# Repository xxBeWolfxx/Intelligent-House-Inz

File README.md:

# Projekt, praca dyplomowa pod tytułem "Układ sterowania inteligentnego budynku mieszkalnego "
Projekt został zrealizowany w ramach pracy dyplomowej na uczelni wyższej, Politechniki Poznańskiej. Miała ona na celu opracowania systemu do zarządzania domostwem.

## Założenia aplikacji: 
### Funkcje aplikacji:
   - Opracowanie układu kontroli i sterowania budynkiem mieszkalnym
   - Opracowanie mobilnego interfejsu uzytkownika
   - Opracowanie układu komunikacji głosowej

Aplikacja składa się z 4 elementów: Komputera (asystent Google'a, serwer, baza danych), Aplikacja (interfejs użytkownika), ESP Sensors (pobieranie danych z czujników), ESP Outputs (zarządzanie załączaniem urządzeń).
## Komputer.

Jako komputer został zaimplementowany komputer Raspberry Pi 4B, który posiada w sobie instancje:
#### Serwer.
Został zrealizowany za pomocą frameworku Django oraz Django REST framework. Została stworzona strona administracyjna do szybkiego modelowania informacji w bazie.
Link: https://github.com/xxBeWolfxx/Django-server

### Baza danych.
Ze względu na wykorzystanie systemu operacyjnego Debian została zaimplementowana baza SQL w dystrybucji MariaDB. Baza posiada tablice: Użytkownik, ESP Sensor, ESP Output. Tablice ESP Sensor oraz ESP Output są w relacji Many-to-Many z tablicą Użytkownik.

#### Asystent.
Asystent został zaimplementowany jako gotowe rozwiązanie GassistPI[www] https://gassistpi-documentation.readthedocs.io. Wymieniony SDK korzysta z rozwiązań Asystenta Google'a. Zostały również dodane skrypty do sterowania płytką ESP Outputs. 

### Płytki PCB.
Zaprojektowano dwa typy płytek w programie Eagle, które są uniwersalne i mają możliwość podłączenia różnych urządzeń. Napięcie zasilające może osiągać wartość od 10 do 20 Voltów DC. 
#### ESP Sensors
Zawiera:
- 4 porty ADC (2x port z 5V, 2x port 3V3),
- 5 portów kontaktronów, badanie statusu pinów czy zostały zwarte czy rozwarte.
- 4 porty magistrali I2C (2x port z 5V, 2x port 3V3).

#### ESP Outputs
- 5 portów przekaźnikowych zasilonych napięciem zasilania. 
- 2 porty do sterowania silnikiem DC.

### Aplikacja
Składa się ona z dwóch aktywności: uwierzytelnienie użytkownika oraz zarządzanie urządzeniami i sensorami w sieci. Zaimplementowano wykresy wartości czujników. Aplikacja współpracuje ściśle z serwerem i komunikuje się z nim po protokole HTTP REST Api.

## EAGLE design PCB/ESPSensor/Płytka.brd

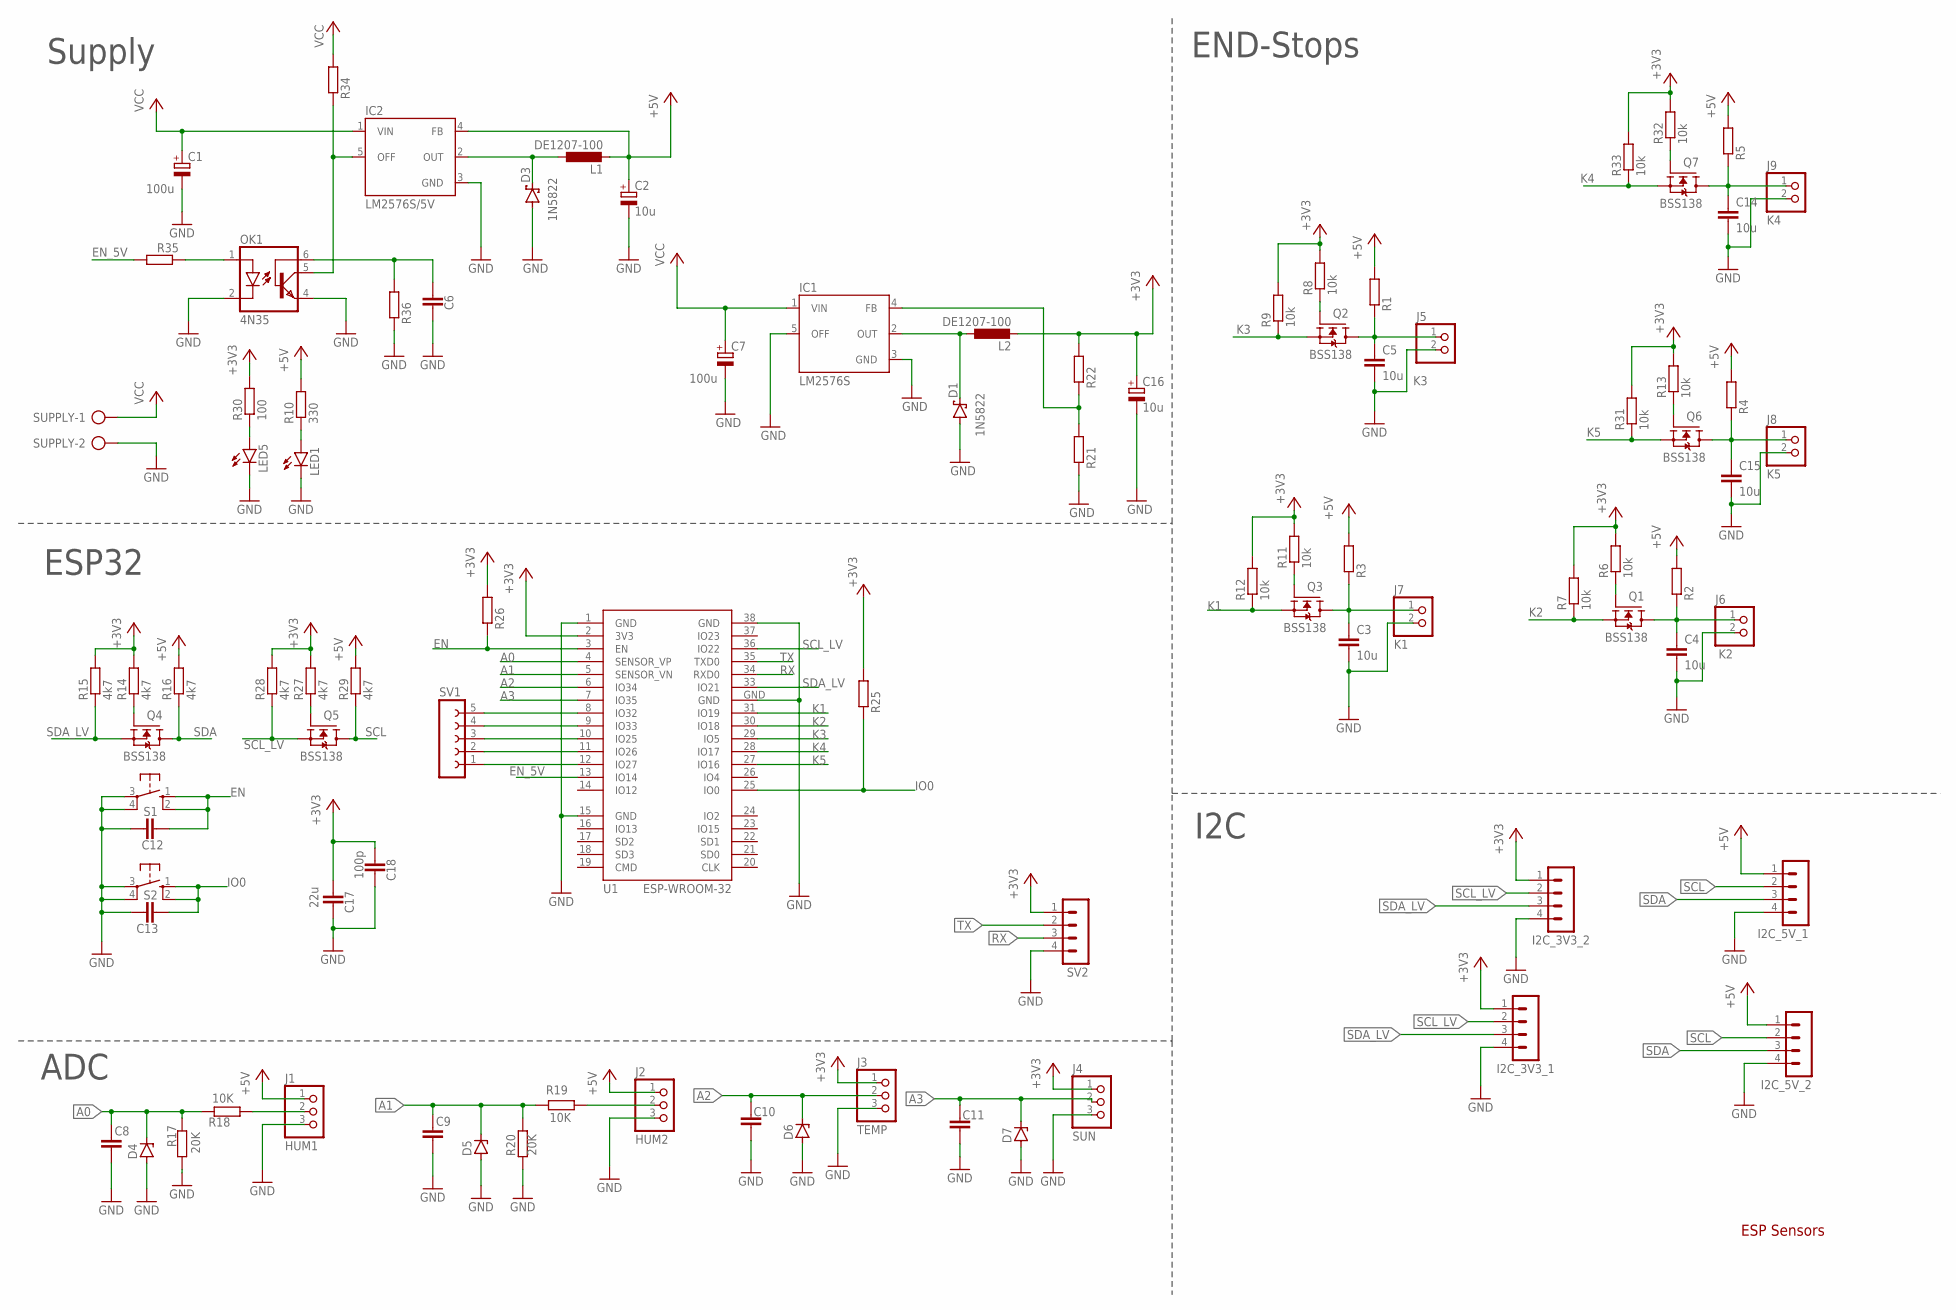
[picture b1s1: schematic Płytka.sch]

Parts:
C1, C7: 100u; E2,5-6
C2, C16: 10u; E3,5-8
C3, C4, C5, C14, C15: 10u; C0805K
C6, C8, C9, C10, C11, C12, C13: C-EUC0805K; C0805K
C17: 22u; C0805K
C18: 100p; C0805K
D1, D3: 1N5822; C4111-15
D4, D5, D6, D7: ZENER-DIODESOD80C; SOD80C
I2C_3V3_1, I2C_3V3_2, I2C_5V_1, I2C_5V_2: MA04-1
IC1: LM2576S; TO263-5
IC2: LM2576S/5V; TO220-5
J1: HUM1; W_TYPE_2MM_3_N
J2: HUM2; W_TYPE_2MM_3_N
J3: TEMP; W_TYPE_2MM_3_N
J4: SUN; W_TYPE_2MM_3_N
J5: K3; W_TYPE_2MM_2_N
J6: K2; W_TYPE_2MM_2_N
J7: K1; W_TYPE_2MM_2_N
J8: K5; W_TYPE_2MM_2_N
J9: K4; W_TYPE_2MM_2_N
L1, L2: DE1207-100; DE1207
LED1, LED5: LEDSML0805; SML0805
OK1: 4N35; DIL06
Q1, Q2, Q3, Q4, Q5, Q6, Q7: BSS138; SOT23
R1, R2, R3, R4, R5, R21, R22, R25, R26, R34, R35, R36: R-EU_R0805; R0805
R6, R7, R8, R9, R11, R12, R13, R31, R32, R33: 10k; R0805
R10: 330; R0805
R14, R15, R16, R27, R28, R29: 4k7; R0805
R17, R20: 20K; R0805
R18, R19: 10K; R0805
R30: 100; R0805
S1, S2: 10-XX; B3F-10XX
SUPPLY: AK500/2-H
SV1: FE05-1
SV2: MA04-1
U1: ESP-WROOM-32

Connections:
+3V3: C16.+, C17.2, C18.2, I2C_3V3_1.1, I2C_3V3_2.1, J3.1, J4.1, L2.2, R6.2, R7.2, R8.2, R9.2, R11.2, R12.2, R13.2, R14.2, R15.2, R22.2, R25.2, R26.2, R27.2, R28.2, R30.2, R31.2, R32.2, R33.2, SV2.1, U1.2 (3V3)
+5V: C2.+, I2C_5V_1.1, I2C_5V_2.1, IC2.4 (FB), J1.1, J2.1, L1.2, R1.2, R2.2, R3.2, R4.2, R5.2, R10.2, R16.2, R29.2
A0: C8.1, D4.C, R17.2, R18.2, U1.4 (SENSOR_VP)
A1: C9.1, D5.C, R19.2, R20.1, U1.5 (SENSOR_VN)
A2: C10.1, D6.C, J3.2, U1.6 (IO34)
A3: C11.1, D7.C, J4.2, U1.7 (IO35)
EN: C12.2, R26.1, S1.1 (S), S1.2 (S1), U1.3 (EN)
EN_5V: R35.2, U1.13 (IO14)
GND: C1.-, C2.-, C3.2, C4.2, C5.2, C6.1, C7.-, C8.2, C9.2, C10.2, C11.2, C12.1, C13.1, C14.2, C15.2, C16.-, C17.1, C18.1, D1.A, D3.A, D4.A, D5.A, D6.A, D7.A, I2C_3V3_1.4, I2C_3V3_2.4, I2C_5V_1.4, I2C_5V_2.4, IC1.3 (GND), IC1.5 (OFF), IC2.3 (GND), J1.3, J2.3, J3.3, J4.3, J5.2, J6.2, J7.2, J8.2, J9.2, LED1.C, LED5.C, OK1.2 (C), OK1.4 (EMI), R17.1, R20.2, R21.1, R36.1, S1.3, S1.4 (P1), S2.3, S2.4 (P1), SUPPLY.2, SV2.4, U1.1 (GND), U1.15 (GND), U1.38 (GND), U1.GND
IO0: C13.2, R25.1, S2.1 (S), S2.2 (S1), U1.25 (IO0)
K1: Q3.2 (S), R12.1, U1.31 (IO19)
K2: Q1.2 (S), R7.1, U1.30 (IO18)
K3: Q2.2 (S), R9.1, U1.29 (IO5)
K4: Q7.2 (S), R33.1, U1.28 (IO17)
K5: Q6.2 (S), R31.1, U1.27 (IO16)
unnamed: C5.1, J5.1, Q2.3 (D), R1.1
unnamed: C4.1, J6.1, Q1.3 (D), R2.1
unnamed: LED1.A, R10.1
unnamed: Q4.1 (G), R14.1
unnamed: C3.1, J7.1, Q3.3 (D), R3.1
unnamed: C14.1, J9.1, Q7.3 (D), R5.1
unnamed: C15.1, J8.1, Q6.3 (D), R4.1
unnamed: Q5.1 (G), R27.1
unnamed: J1.2, R18.1
unnamed: SV1.5, U1.8 (IO32)
unnamed: Q1.1 (G), R6.1
unnamed: SV1.4, U1.9 (IO33)
unnamed: Q2.1 (G), R8.1
unnamed: SV1.3, U1.10 (IO25)
unnamed: Q3.1 (G), R11.1
unnamed: SV1.2, U1.11 (IO26)
unnamed: J2.2, R19.1
unnamed: D3.C, IC2.2 (OUT), L1.1
unnamed: Q6.1 (G), R13.1
unnamed: D1.C, IC1.2 (OUT), L2.1
unnamed: SV1.1, U1.12 (IO27)
unnamed: LED5.A, R30.1
unnamed: Q7.1 (G), R32.1
unnamed: IC2.5 (OFF), OK1.5 (COL), R34.1
unnamed: OK1.1 (A), R35.1
unnamed: C6.2, OK1.6 (BAS), R36.2
unnamed: IC1.4 (FB), R21.2, R22.1
RX: SV2.3, U1.34 (RXD0)
SCL: I2C_5V_1.2, I2C_5V_2.2, Q5.3 (D), R29.1
SCL_LV: I2C_3V3_1.2, I2C_3V3_2.2, Q5.2 (S), R28.1, U1.36 (IO22)
SDA: I2C_5V_1.3, I2C_5V_2.3, Q4.3 (D), R16.1
SDA_LV: I2C_3V3_1.3, I2C_3V3_2.3, Q4.2 (S), R15.1, U1.33 (IO21)
TX: SV2.2, U1.35 (TXD0)
VCC: C1.+, C7.+, IC1.1 (VIN), IC2.1 (VIN), R34.2, SUPPLY.1

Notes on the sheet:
Supply
ESP32
ADC
I2C
END-Stops
ESP Sensors

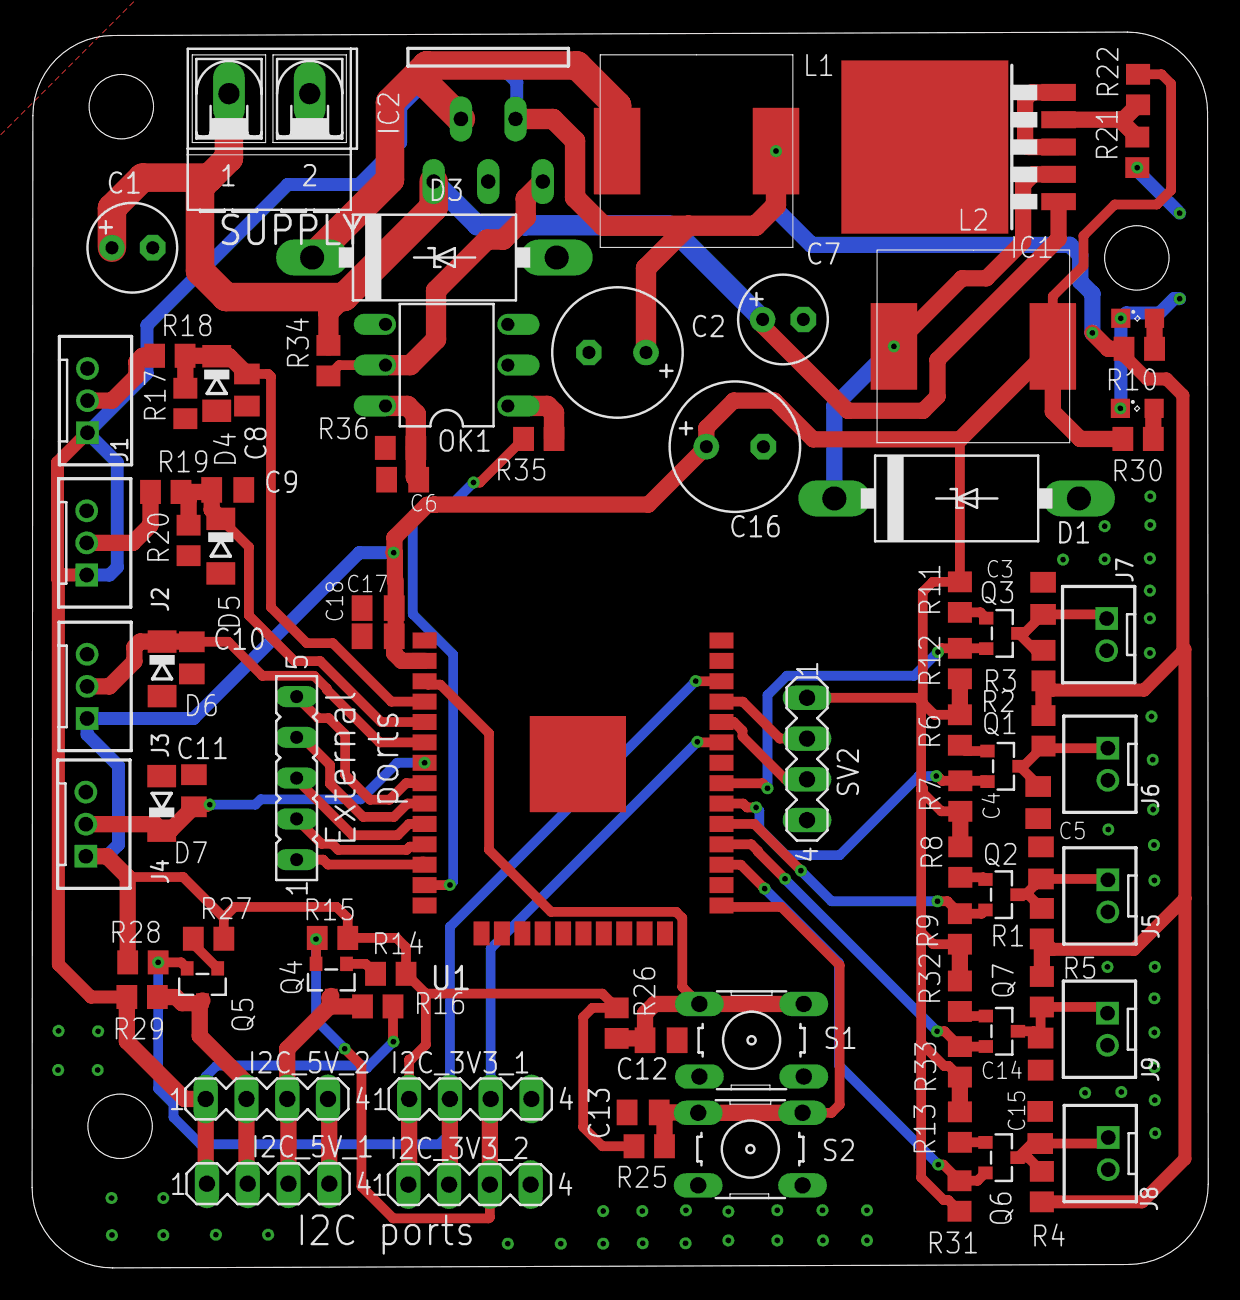
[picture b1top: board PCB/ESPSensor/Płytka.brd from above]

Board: 2 copper layers, 73.3 x 77.0 mm, 91 parts (0 on the bottom side), 49 nets.

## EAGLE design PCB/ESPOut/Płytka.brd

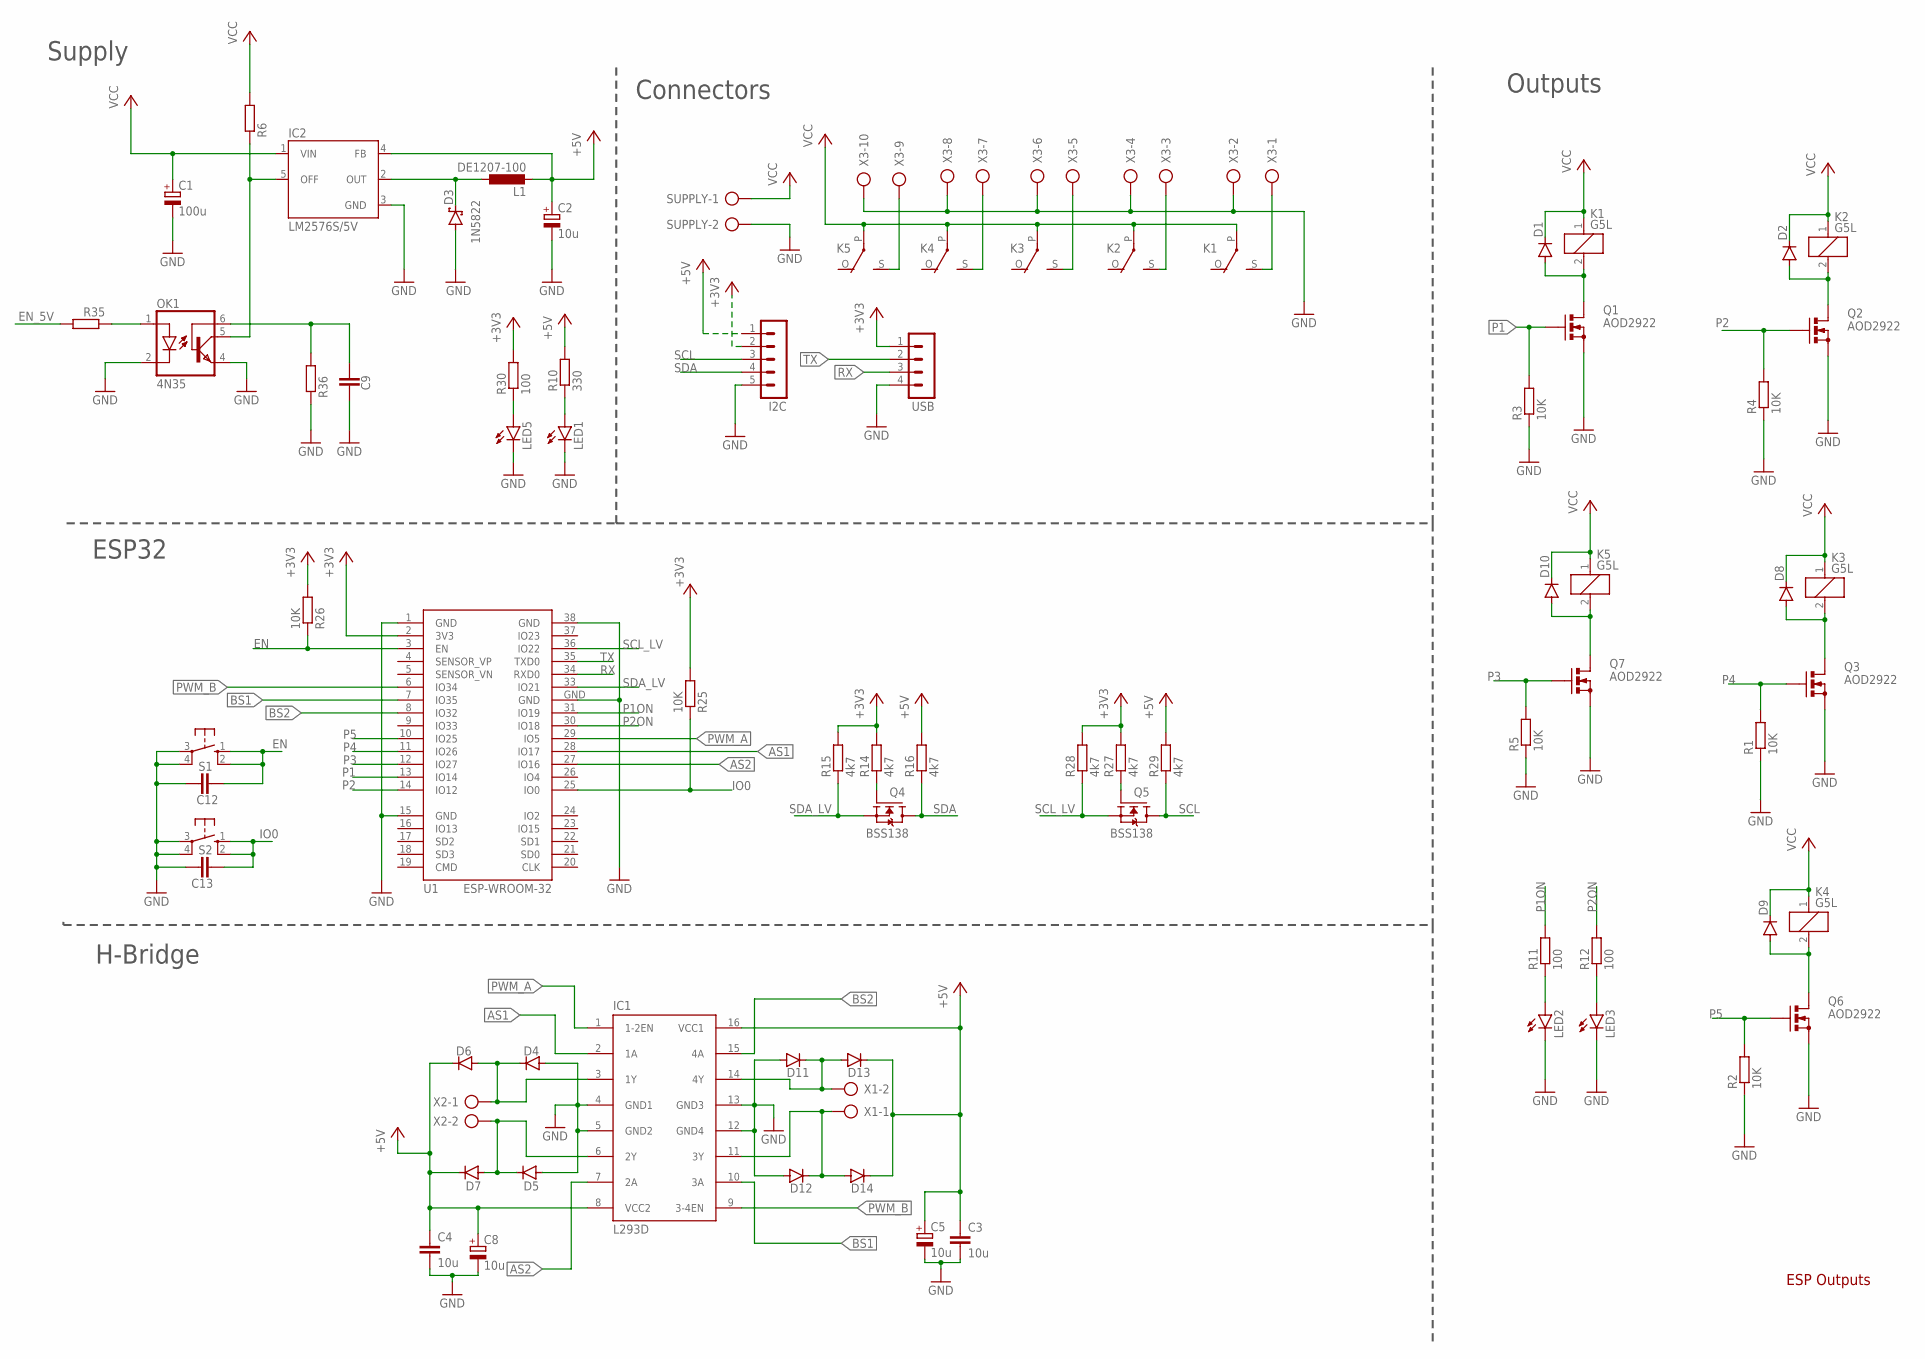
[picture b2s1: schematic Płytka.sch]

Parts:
C1: 100u; E2,5-6
C2: 10u; E3,5-8
C3, C4: 10u; C0805K
C5, C8: 10u; E5-8,5
C9, C12, C13: C-EUC0805K; C0805K
D1, D2, D4, D5, D6, D7, D8, D9, D10, D11, D12, D13, D14: DIODE-DO214AC; DO214AC
D3: 1N5822; C4111-15
I2C: MA05-1
IC1: L293D; DIL16
IC2: LM2576S/5V; TO220-5
K1, K2, K3, K4, K5: G5L; G5LE
L1: DE1207-100; DE1207
LED1, LED2, LED3, LED5: LEDSML0805; SML0805
OK1: 4N35; DIL06
Q1, Q2, Q3, Q6, Q7: AOD2922; TO252AA
Q4, Q5: BSS138; SOT23
R1, R2, R3, R4, R5, R25, R26: 10K; R0805
R6, R35, R36: R-EU_R0805; R0805
R10: 330; R0805
R11, R12, R30: 100; R0805
R14, R15, R16, R27, R28, R29: 4k7; R0805
S1, S2: 10-XX; B3F-10XX
SUPPLY: AK500/2-H
U1: ESP-WROOM-32
USB: MA04-1
X1, X2: AK500/2
X3: AK500/10

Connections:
+3V3: I2C.2, R14.2, R15.2, R25.2, R26.2, R27.2, R28.2, R30.2, U1.2 (3V3), USB.1
+5V: C2.+, C3.1, C4.1, C5.+, C8.+, D6.C, D7.C, D13.C, D14.C, I2C.1, IC1.8 (VCC2), IC1.16 (VCC1), IC2.4 (FB), L1.2, R10.2, R16.2, R29.2
AS1: IC1.2 (1A), U1.28 (IO17)
AS2: IC1.7 (2A), U1.27 (IO16)
BS1: IC1.10 (3A), U1.7 (IO35)
BS2: IC1.15 (4A), U1.8 (IO32)
EN: C12.2, R26.1, S1.1 (S), S1.2 (S1), U1.3 (EN)
EN_5V: R35.2
GND: C1.-, C2.-, C3.2, C4.2, C5.-, C8.-, C9.1, C12.1, C13.1, D3.A, D4.A, D5.A, D11.A, D12.A, I2C.5, IC1.4 (GND1), IC1.5 (GND2), IC1.12 (GND4), IC1.13 (GND3), IC2.3 (GND), LED1.C, LED2.C, LED3.C, LED5.C, OK1.2 (C), OK1.4 (EMI), Q1.2 (S), Q2.2 (S), Q3.2 (S), Q6.2 (S), Q7.2 (S), R1.1, R2.1, R3.1, R4.1, R5.1, R36.1, S1.3, S1.4 (P1), S2.3, S2.4 (P1), SUPPLY.2, U1.1 (GND), U1.15 (GND), U1.38 (GND), U1.GND, USB.4, X3.2, X3.4, X3.6, X3.8, X3.10
IO0: C13.2, R25.1, S2.1 (S), S2.2 (S1), U1.25 (IO0)
unnamed: K5.S, X3.9
unnamed: D8.A, K3.2, Q3.3 (D)
unnamed: LED1.A, R10.1
unnamed: Q4.1 (G), R14.1
unnamed: LED2.A, R11.1
unnamed: LED3.A, R12.1
unnamed: K4.S, X3.7
unnamed: Q5.1 (G), R27.1
unnamed: K3.S, X3.5
unnamed: K2.S, X3.3
unnamed: D9.A, K4.2, Q6.3 (D)
unnamed: D1.A, K1.2, Q1.3 (D)
unnamed: D2.A, K2.2, Q2.3 (D)
unnamed: K1.S, X3.1
unnamed: IC2.5 (OFF), OK1.5 (COL), R6.1
unnamed: D10.A, K5.2, Q7.3 (D)
unnamed: D4.C, D6.A, IC1.3 (1Y), X2.1
unnamed: D3.C, IC2.2 (OUT), L1.1
unnamed: D12.C, D14.A, IC1.11 (3Y), X1.1
unnamed: D11.C, D13.A, IC1.14 (4Y), X1.2
unnamed: LED5.A, R30.1
unnamed: D5.C, D7.A, IC1.6 (2Y), X2.2
unnamed: OK1.1 (A), R35.1
unnamed: C9.2, OK1.6 (BAS), R36.2
P1: Q1.1 (G), R3.2, U1.13 (IO14)
P1ON: R11.2, U1.31 (IO19)
P2: Q2.1 (G), R4.2, U1.14 (IO12)
P2ON: R12.2, U1.30 (IO18)
P3: Q7.1 (G), R5.2, U1.12 (IO27)
P4: Q3.1 (G), R1.2, U1.11 (IO26)
P5: Q6.1 (G), R2.2, U1.10 (IO25)
PWM_A: IC1.1 (1-2EN), U1.29 (IO5)
PWM_B: IC1.9 (3-4EN), U1.6 (IO34)
RX: U1.34 (RXD0), USB.3
SCL: I2C.3, Q5.3 (D), R29.1
SCL_LV: Q5.2 (S), R28.1, U1.36 (IO22)
SDA: I2C.4, Q4.3 (D), R16.1
SDA_LV: Q4.2 (S), R15.1, U1.33 (IO21)
TX: U1.35 (TXD0), USB.2
VCC: C1.+, D1.C, D2.C, D8.C, D9.C, D10.C, IC2.1 (VIN), K1.1, K1.P, K2.1, K2.P, K3.1, K3.P, K4.1, K4.P, K5.1, K5.P, R6.2, SUPPLY.1

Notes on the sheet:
Supply
Connectors
Outputs
ESP32
H-Bridge
ESP Outputs

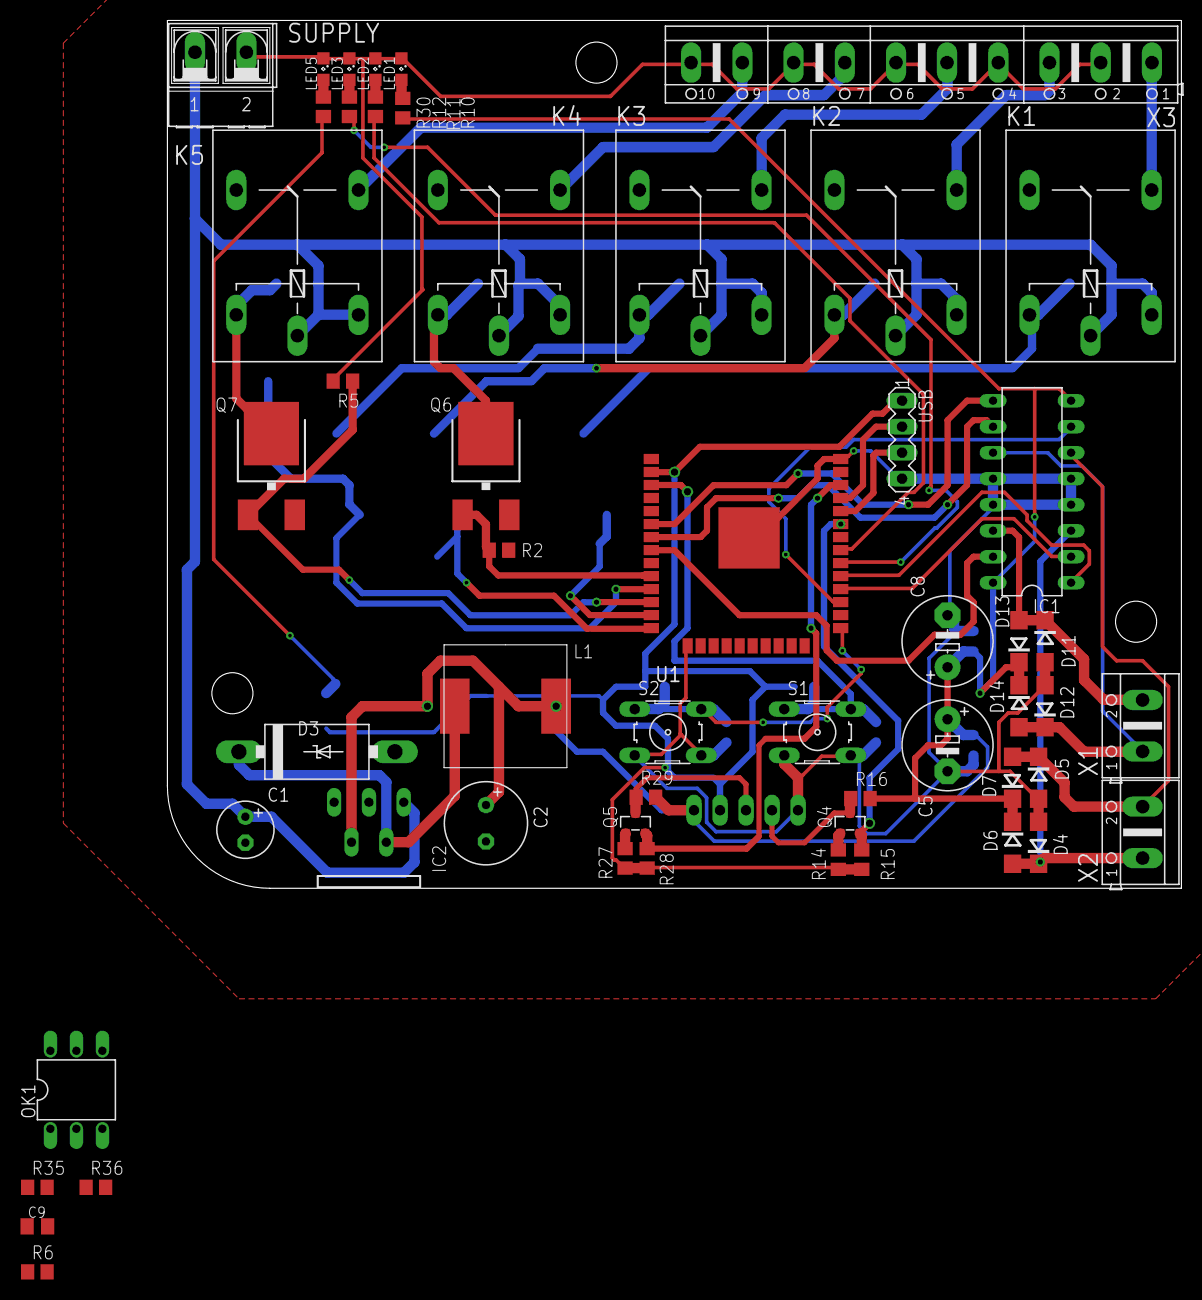
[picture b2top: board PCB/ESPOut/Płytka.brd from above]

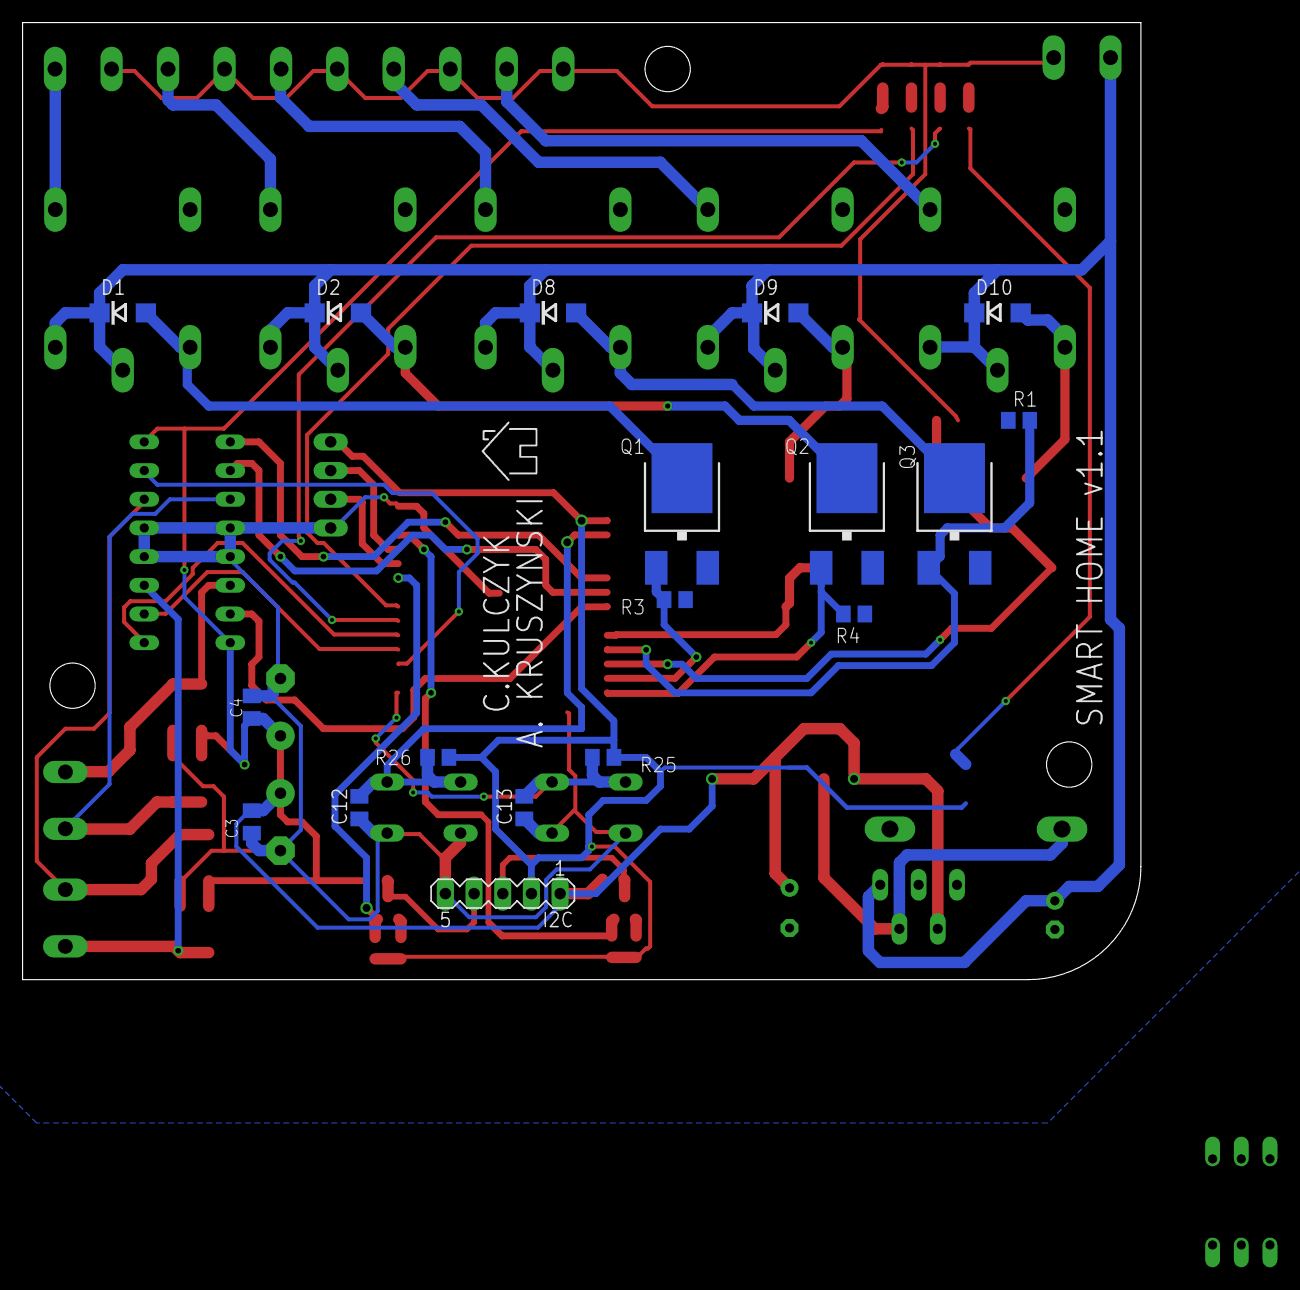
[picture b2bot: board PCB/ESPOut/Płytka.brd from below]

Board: 2 copper layers, 99.0 x 84.8 mm, 72 parts (18 on the bottom side), 49 nets.

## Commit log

2020-10-04 Diagram
2020-10-17 no message
2020-10-17 Init Android
2020-10-17 Add basic SplashScreen
2020-10-19 Add RPi's schematic
2020-10-20 Add database handling
2020-10-22 Fix bugs
2020-10-22 Add gitignore
2020-10-22 improve gitignore
2020-10-22 login_activity layout
2020-10-23 Add new things
2020-10-30 Add nav_viewer
2020-10-31 End migration to AndroidX, add nav_side
2020-11-01 Add fragments and they are activated in nav_menu
2020-11-15 Add PCBs
2020-12-03 Add new PCBs
2020-12-10 menu, buttons
2020-12-10 Conflict resolve
2020-12-10 Clean up project
2020-12-12 Make getUser function, add progress bar for loading data
2020-12-12 Add loading screen
2020-12-12 temp graph
2020-12-13 Add animation, Get objects from database
2021-01-02 Add new fragments
2021-01-03 Add function of login and deserialization
2021-01-04 Add method to generate a list of ESPs, add two fragments
2021-01-04 errorsssy
2021-01-05 add inputs, outputs layouts; refresh button; charts modifications
2021-01-16 Configure connection between app and database
2021-01-21 Add new buttons
2021-01-25 add function to spinner
2021-02-02 Creating charts
2021-02-21 Add readme
2021-05-04 Add new method of controling the supply
2021-08-24 Finished PCB Sensor

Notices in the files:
parts and their libraries:
esp32: Creative Commons Attribution-ShareAlike 4.0 International
